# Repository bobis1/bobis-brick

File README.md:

# bobis-brick
 A console I am  working for hack club's create your own console challenge. This includes a game, a controller pcb, a controller case(For the actual console I play on making it inside a suitcase) 

## Tower Game
This is the game that I created for the console.

### Controls
###### W/Space: Jump
###### A: Move Left
###### D: Move right
###### R: Reload Spells
###### Q: firebolt spell
###### E: burst spell
###### F: Super Jump spell

### About the game
In this game you defeat waves of enemies such as flying fireballs and rolling rocks as the tower keeps growing towards the sky.

## Controller
This is the pcb for the controller. It has two joysticks with 1 controlling the mouse and another controlling the movements.

### Parts
2x COM-09032 joysticks
1x Seeed Studio XIAO RP2040
3x Push switch

### Controls
Left joystick, WASD
Right joystick, Arrow Keys(set up to control mouse)
3 buttons, for each button of the game.

## Case
This is a basic case for the controller. I intend of creating a case for the console out of a suit case once I get the physical console. My plan was to glue the case lid on. You should be able to just put the pcb directly into the case.

## Launcher App
This is a basic launcher app for the launcher. Currently it can launch the Tower game as well as being able to launch other apps. To use this you either click the Tower game button assuming that it is set up correctly or you use the add app button on the bottom. 

### Todo: 
I would like to make it so that it scans for executables in a certain folder.

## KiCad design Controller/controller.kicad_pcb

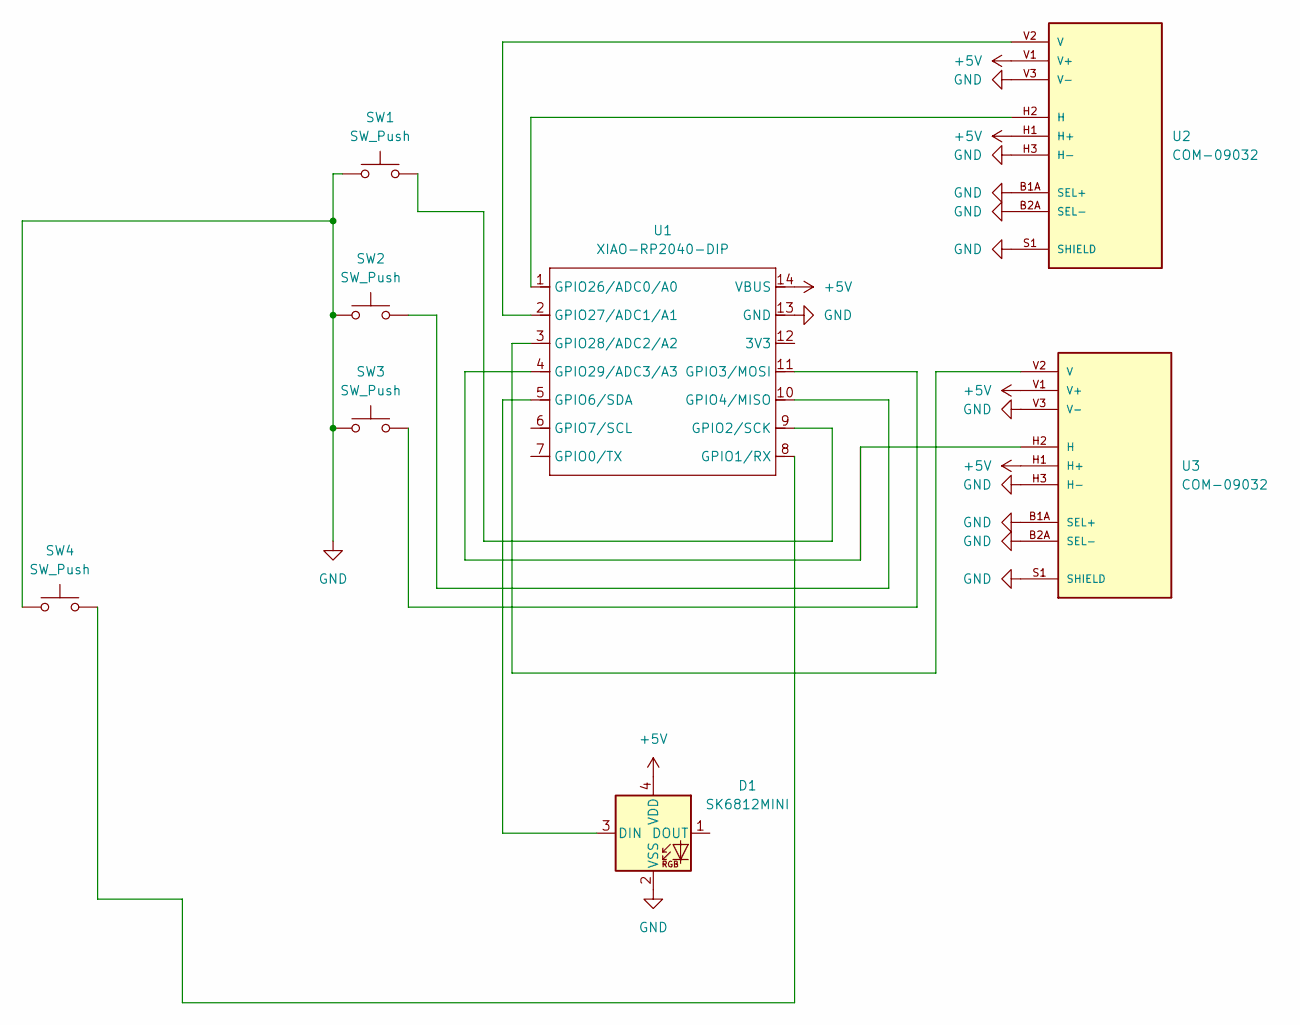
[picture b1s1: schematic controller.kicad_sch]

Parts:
D1: SK6812MINI; LED_SK6812MINI_PLCC4_3.5x3.5mm_P1.75mm
SW1, SW2, SW3, SW4: SW_Push; SW_Cherry_MX_1.00u_PCB
U1: XIAO-RP2040-DIP
U2, U3: COM-09032; XDCR_COM-09032; PARTREV N/A

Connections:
+5V: D1.4 (VDD), U1.14 (VBUS), U2.H1 (H+), U2.V1 (V+), U3.H1 (H+), U3.V1 (V+)
GND: D1.2 (VSS), SW1.1, SW2.1, SW3.1, SW4.1, U1.13 (GND), U2.B1A (SEL+), U2.B2A (SEL-), U2.H3 (H-), U2.S1 (SHIELD), U2.S2 (SHIELD), U2.S3 (SHIELD), U2.S4 (SHIELD), U2.V3 (V-), U3.B1A (SEL+), U3.B2A (SEL-), U3.H3 (H-), U3.S1 (SHIELD), U3.S2 (SHIELD), U3.S3 (SHIELD), U3.S4 (SHIELD), U3.V3 (V-)
unnamed: D1.3 (DIN), U1.5 (GPIO6/SDA)
unnamed: SW4.2, U1.8 (GPIO1/RX)
unnamed: SW1.2, U1.9 (GPIO2/SCK)
unnamed: SW3.2, U1.11 (GPIO3/MOSI)
unnamed: SW2.2, U1.10 (GPIO4/MISO)
unnamed: U1.1 (GPIO26/ADC0/A0), U2.H2 (H)
unnamed: U1.2 (GPIO27/ADC1/A1), U2.V2 (V)
unnamed: U1.3 (GPIO28/ADC2/A2), U3.V2 (V)
unnamed: U1.4 (GPIO29/ADC3/A3), U3.H2 (H)

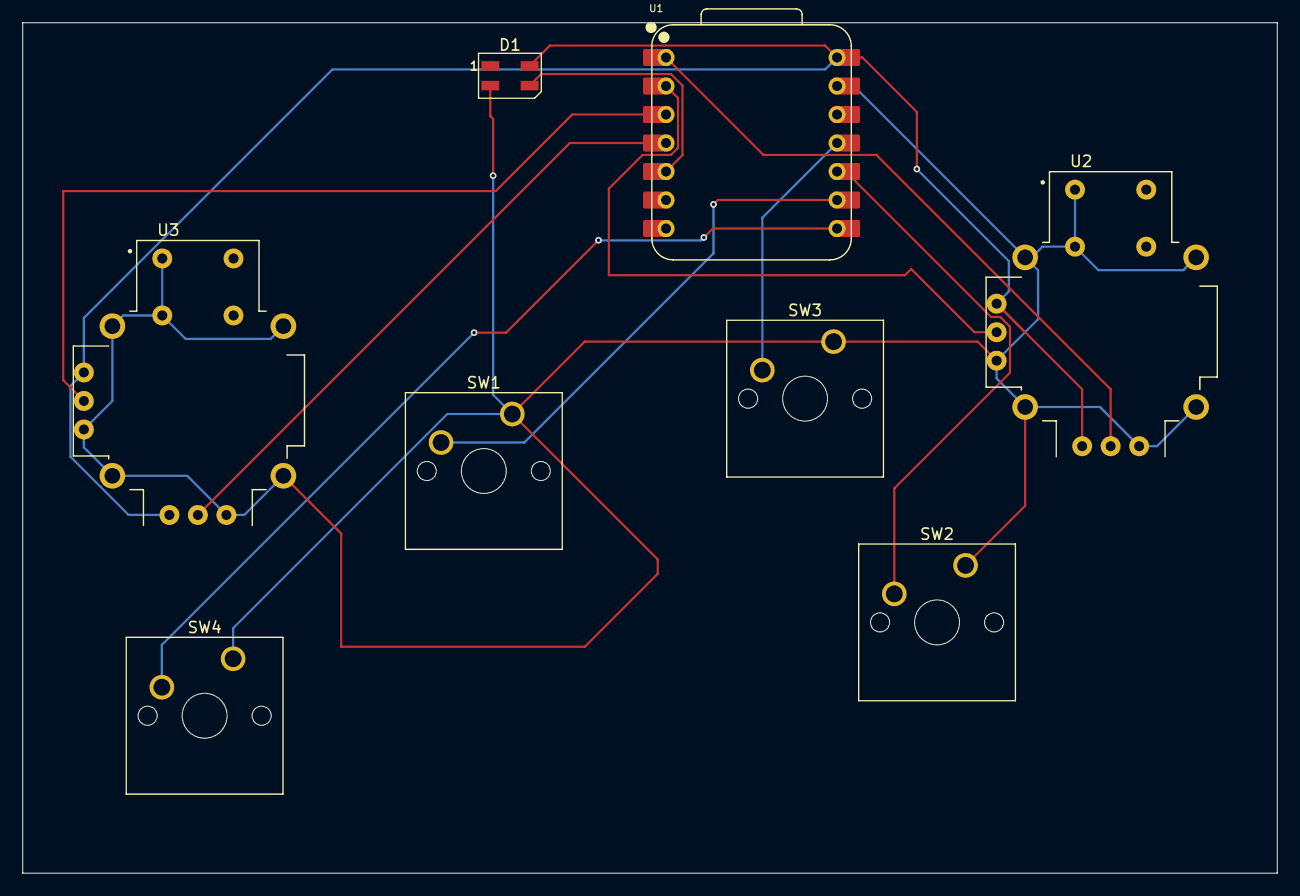
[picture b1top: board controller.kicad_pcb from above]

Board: 2 copper layers, 111.8 x 75.8 mm, 8 parts (0 on the bottom side), 11 nets.

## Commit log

2026-01-01 Added some of the basic structure of the project
2026-01-01 Tried for ages to get player controls to work only to realize that there was a template for it all this time
2026-01-04 Added a tilemap thing
2026-01-05 Worked on game
    Added enemy and projectile. More details in journal.md
2026-01-05 video in journal
2026-01-05 Fixed the video
2026-01-06 Added enemy spawner
2026-01-06 Added the progress for Jan 5,
    Added more enemy features
    Added platform generation
2026-01-07 Added more enemies and made the projectiles point at the cursor
2026-01-07 Added some enemies and worked on some polish
    Today, there was not alot of work that was done :(. However I added a new flying enemy along with a roof so that the player will not be able to just jump outside the playing area. Also the projectile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
2026-01-08 Added more types of platforms
2026-01-08 Added some more assets
2026-01-08 Added logs
2026-01-09 Added textures and a clip system
2026-01-09 Added journal log for jan 7
2026-01-09 Added enemy waves and fixed the ammo ui
2026-01-09 Added assets
2026-01-11 Added more spells and QOL
2026-01-12 Added some journal entries
    starting week 2:)
2026-01-13 Added three buttons and kinda added a joystick
2026-01-13 added libs
2026-01-14 Day 2 of controller
2026-01-14 Connected the GND and set stuff up
    Next do the firmware and the case
2026-01-16 Added firmware
2026-01-16 (I think) I finished the firmware for the controller
2026-01-16 Journaling
2026-01-20 Added JavaFX app where launcher will work
2026-01-20 Added basic stuff and journalled
2026-01-22 Added app launch functionality
2026-01-23 Added icon and cleaned up project
2026-01-27 Added some journal logs and stuff
2026-01-27 Added file picker
2026-01-27 fixed project structure
2026-01-30 success with build
2026-01-30 removed extra fluff
2026-01-30 create gerber file
2026-02-06 added stuff to game
2026-02-08 added BOM and worked abit on the game
2026-03-09 Basic readme done
2026-03-13 Updated firmware and updated readme
2026-03-15 fixed image
